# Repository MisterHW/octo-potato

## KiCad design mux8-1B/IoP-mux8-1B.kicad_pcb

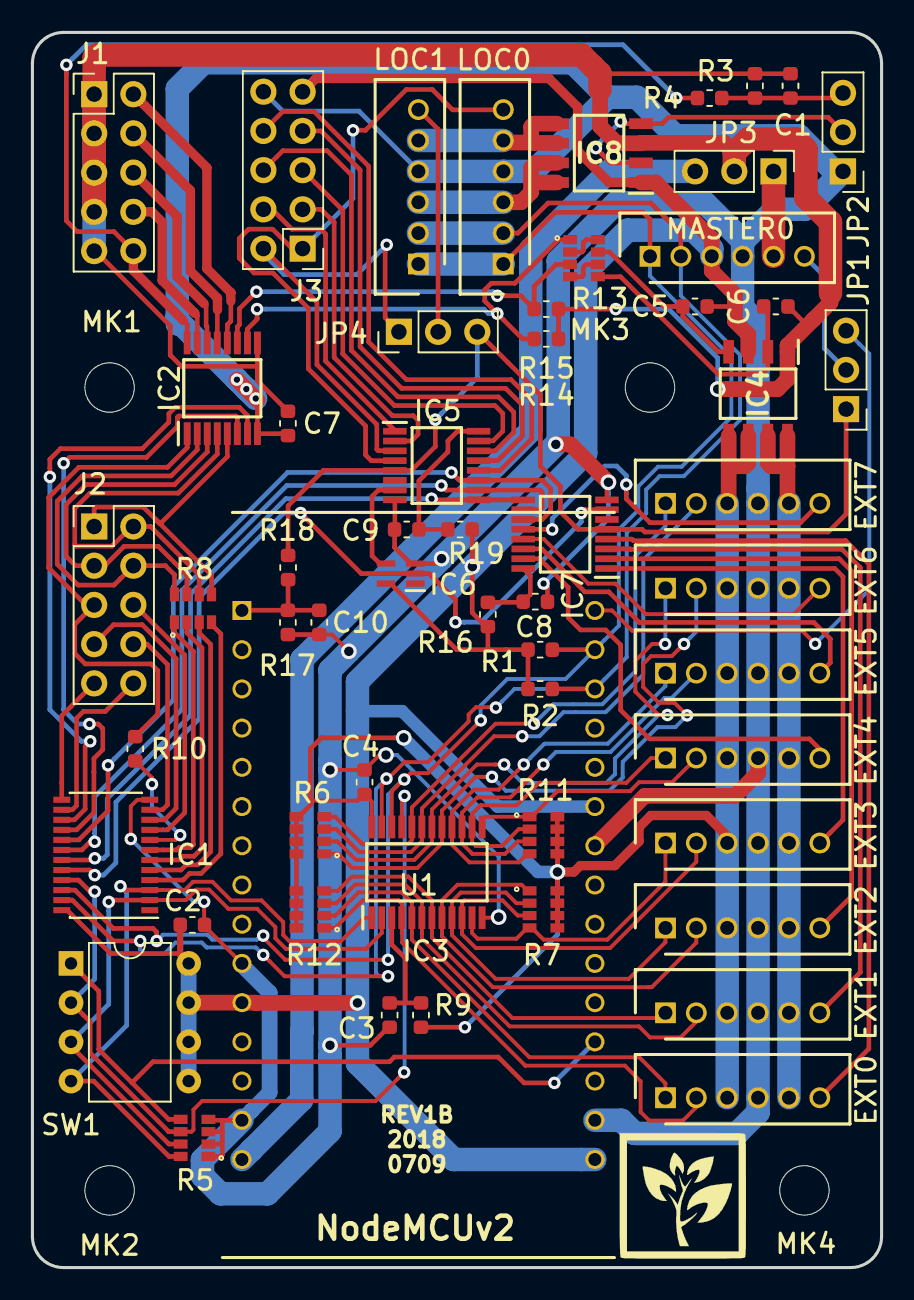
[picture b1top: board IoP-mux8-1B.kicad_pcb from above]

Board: 2 copper layers, 55.0 x 80.0 mm, 61 parts (0 on the bottom side), 90 nets.

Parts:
C1, C5, C6, C7: 1µF; C_0603_1608Metric
C2, C3, C4, C8, C9: 100n; C_0603_1608Metric
C10: 100nF; C_0603_1608Metric
EXT0, EXT1, EXT2, EXT3, EXT4, EXT5, EXT6, EXT7: B6B-PH-K-S(LF)(SN); SHDR6W50P0X200_1X6_1390X450X600P
IC1: TCA9535PWR; TSSOP-24_4.4x7.8mm_P0.65mm
IC2: TPL7407LPWR; SOP65P640X120-16N
IC3: PCA9548APW; SOP65P640X120-24N
IC4, IC8: SI4925DDY-T1-GE3; SOIC127P600X175-8N
IC5, IC7: PI5C3251QE; SOP64P599X175-16N
IC6: SN74LVC1G04QDCKRQ1; SOT65P210X110-5N
J1, J2, J3: Conn_02x05_Odd_Even; PinHeader_2x05_P2.54mm_Vertical
JP1, JP2, JP3, JP4: Jumper_3_Bridged12; PinHeader_1x03_P2.54mm_Vertical
LOC0, LOC1: B6B-PH-K-S(LF)(SN); SHDR6W50P0X200_1X6_1390X450X600P
MASTER0: B6B-PH-K-S(LF)(SN); SHDR6W50P0X200_1X6_1390X450X600P
MK1, MK2, MK3, MK4: Mounting_Hole; MountingHole_3.2mm_M3
R1, R2, R4, R9: 4.7k; R_0603_1608Metric
R3, R14, R15: 470k; R_0603_1608Metric
R5, R6, R7, R11, R12, R13: BCN164AB472J7; YC164
R8: YC164-FR-07220RL; YC164
R10, R16, R19: 220; R_0603_1608Metric
R17: NC; R_0603_1608Metric
R18: 220R; R_0603_1608Metric
SW1: SW_DIP_x04; DIP-8_W7.62mm
U1: ESP8266-NodeMCUv2; DIP2286W64P254L4826H735Q30N

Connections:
3.3V_IN: C2.1, C5.2, IC1.24, IC4.3, IC6.5, IC8.1, J3.9, MASTER0.3, R1.2, R2.2, R16.2, R19.2, SW1.5, SW1.6, SW1.7, SW1.8, U1.11, U1.16, U1.25
3.3V_SW_G: C5.1, IC4.4, R13.6
/3.3V_LOC: IC8.7, IC8.8, LOC0.3, LOC1.3
/3.3V_SW: C4.2, EXT0.3, EXT1.3, EXT2.3, EXT3.3, EXT4.3, EXT5.3, EXT6.3, EXT7.3, IC3.24, IC4.5, IC4.6, R6.5, R6.6, R6.7, R6.8, R7.5, R7.6, R7.7, R7.8, R9.2, R11.5, R11.6, R11.7, R11.8, R12.5, R12.6, R12.7, R12.8
/A0: EXT0.6, IC7.4
/A1: EXT1.6, IC7.3
/A2: EXT2.6, IC7.2
/A3: EXT3.6, IC7.1
/A4: EXT4.6, IC7.15
/A5: EXT5.6, IC7.14
/A6: EXT6.6, IC7.13
/A7: EXT7.6, IC7.12
/ENA_OUT: JP1.3, U1.30
/I2C-Analog-Expander/3.3V_CTRL: IC1.15, IC2.7
/I2C-Analog-Expander/GPIO0: IC1.4, R8.4
/I2C-Analog-Expander/GPIO1: IC1.5, R8.3
/I2C-Analog-Expander/GPIO2: IC1.6, R8.2
/I2C-Analog-Expander/GPIO3: IC1.7, R8.1
/I2C-Analog-Expander/GPIO4: IC1.8, R10.1
/I2C-Analog-Expander/VBAT_CTRL: IC1.16, IC2.6
/M_OUT: JP1.2, MASTER0.6
/M_PWR: JP3.1, MASTER0.5
/M_SCL: IC1.22, IC3.22, LOC0.1, LOC1.1, MASTER0.1, R1.1, U1.29
/M_SDA: IC1.23, IC3.23, LOC0.2, LOC1.2, MASTER0.2, R2.1, U1.28
/SCL0: EXT0.1, IC3.5, R6.2
/SCL1: EXT1.1, IC3.7, R6.4
/SCL2: EXT2.1, IC3.9, R7.2
/SCL3: EXT3.1, IC3.11, R7.4
/SCL4: EXT4.1, IC3.14, R11.2
/SCL5: EXT5.1, IC3.16, R11.4
/SCL6: EXT6.1, IC3.18, R12.2
/SCL7: EXT7.1, IC3.20, R12.4
/SDA0: EXT0.2, IC3.4, R6.1
/SDA1: EXT1.2, IC3.6, R6.3
/SDA2: EXT2.2, IC3.8, R7.1
/SDA3: EXT3.2, IC3.10, R7.3
/SDA4: EXT4.2, IC3.13, R11.1
/SDA5: EXT5.2, IC3.15, R11.3
/SDA6: EXT6.2, IC3.17, R12.1
/SDA7: EXT7.2, IC3.19, R12.3
/VBAT_LOC: IC8.5, IC8.6, LOC0.5, LOC1.5
/VBAT_SW: EXT0.5, EXT1.5, EXT2.5, EXT3.5, EXT4.5, EXT5.5, EXT6.5, EXT7.5, IC4.7, IC4.8
A8: IC5.4, J3.1, LOC0.6
A9: IC5.3, J3.2, JP4.1
A10: IC5.2, J3.3
A11: IC5.1, J3.4
A12: IC5.15, J3.5
A13: IC5.14, J3.6
A14: IC5.13, J3.7
A15: IC5.12, J3.8
ADDR0: IC1.3, IC3.1, R5.5, SW1.4
ADDR1: IC1.2, IC3.2, R5.6, SW1.3
ADDR2: IC1.21, IC3.21, R5.7, SW1.2
AMUX0: IC1.17, IC5.11, IC7.11
AMUX1: IC1.18, IC5.10, IC7.10
AMUX2: IC1.19, IC5.9, IC7.9
AMUX3: IC1.20, IC6.2, IC7.7
DIP4: R5.8, SW1.1, U1.19
GND: C2.2, C3.2, C4.1, C7.2, C8.1, C9.2, C10.1, EXT0.4, EXT1.4, EXT2.4, EXT3.4, EXT4.4, EXT5.4, EXT6.4, EXT7.4, IC1.12, IC2.8, IC3.12, IC5.8, IC6.3, IC7.8, J3.10, JP2.1, LOC0.4, LOC1.4, MASTER0.4, R5.1, R5.2, R5.3, R5.4, R17.2, U1.10, U1.14, U1.17, U1.24
GPIO5: IC1.9, J2.6
GPIO6: IC1.10, J2.7
GPIO7: IC1.11, J2.8
GPIO8: IC1.13, J2.9
GPIO9: IC1.14, J2.10
M_ANA: IC5.5, IC7.5, JP1.1, JP4.3, R18.2
unnamed: C1.1, JP2.3, R3.1, R4.2
unnamed: C3.1, IC3.3, R9.1
unnamed: C8.2, IC7.16, R16.1
unnamed: C9.1, IC5.16, R19.1
unnamed: C10.2, R17.1, R18.1, U1.1
unnamed: IC2.10, R13.1, R14.2
unnamed: IC2.11, R13.3, R15.2
unnamed: IC5.7, IC6.4
unnamed: IC8.2, IC8.4, JP2.2
unnamed: JP4.2, LOC1.6
unnamed: R13.2, R13.5
unnamed: R13.4, R13.7
PSW0: IC2.12, J1.2
PSW1: IC2.13, J1.4
PSW2: IC2.14, J1.6
PSW3: IC2.15, J1.8
PSW4: IC2.16, J1.10, R4.1
SWIO0: IC2.5, J2.1, R8.8
SWIO1: IC2.4, J2.2, R8.7
SWIO2: IC2.3, J2.3, R8.6
SWIO3: IC2.2, J2.4, R8.5
SWIO4: IC2.1, J2.5, R10.2
VBAT_IN: C1.2, C6.2, C7.1, IC2.9, IC4.1, IC8.3, J1.1, J1.3, J1.5, J1.7, J1.9, JP3.2, R3.2, R14.1, R15.1
VBAT_SW_G: C6.1, IC4.2, R13.8
VUSB: JP3.3, U1.15
